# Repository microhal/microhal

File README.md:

devel: 

# microhal
Microhal is project that try to deliver Hardware Abstraction Layer (HAL) that helps you develop software faster and easier to portable to different platforms.

## microhal API
We provide API for:
- GPIO
- External Inettupts
- Serial Ports
- SPI
- I2C

## Supported platforms
STM32F4xx, STM32F3xx <br>
Currently we are testing our software on:<br>
- STM32F407VGT6
- STM32F411RE
- STM32F344R8

## Device drivers
With microhal we provide device drivers working above our HAL.
List of supported devices:
- BMP180
- DS2782
- DS2786
- HX711 (SPI Implementation)
- ISL29023
- Lepton IR Cammera
- LIS2DH12
- LIS302
- LIS3DSH
- LSM330DL
- M24C16
- MAG3110
- MPL115A2
- MPL3115A2
- MRF89XA
- PCF8563
- RFM70
- SHT21
- TMP006
- uCAM-II
- WS2812 (SPI Implementation)

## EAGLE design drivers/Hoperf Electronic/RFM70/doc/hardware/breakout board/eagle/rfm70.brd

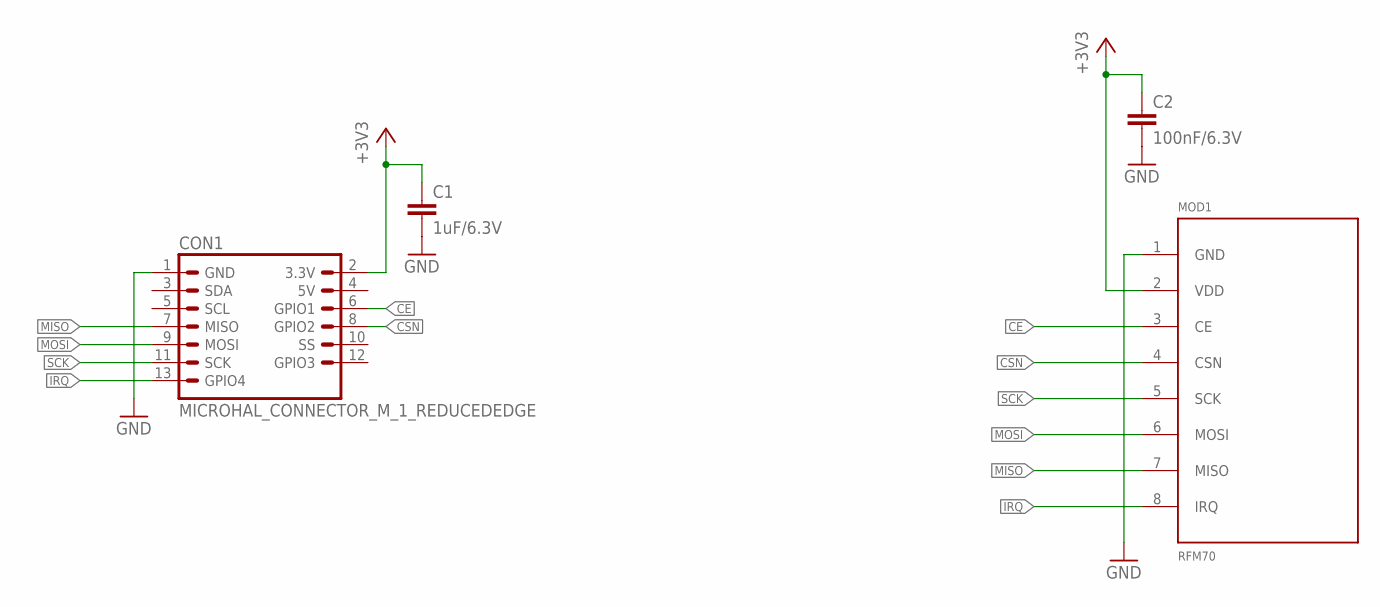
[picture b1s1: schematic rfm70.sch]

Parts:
C1: 1uF/6.3V; C0603K
C2: 100nF/6.3V; C0603K
CON1: MICROHAL_CONNECTOR_M_1_REDUCEDEDGE; MICROHAL_CONNECTOR_M_1_REDUCED_EDGE
MOD1: RFM70; RFM70_PACK

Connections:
+3V3: C1.1, C2.1, CON1.2 (3.3V), MOD1.2 (VDD)
CE: CON1.6 (GPIO1), MOD1.3 (CE)
CSN: CON1.8 (GPIO2), MOD1.4 (CSN)
GND: C1.2, C2.2, CON1.1 (GND), MOD1.1 (GND)
IRQ: CON1.13 (GPIO4), MOD1.8 (IRQ)
MISO: CON1.7 (MISO), MOD1.7 (MISO)
MOSI: CON1.9 (MOSI), MOD1.6 (MOSI)
SCK: CON1.11 (SCK), MOD1.5 (SCK)

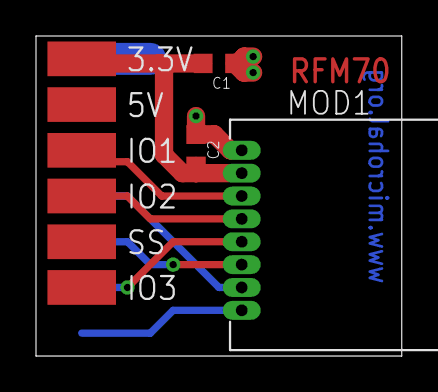
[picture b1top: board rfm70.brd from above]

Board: 2 copper layers, 20.3 x 17.8 mm, 4 parts (0 on the bottom side), 8 nets.

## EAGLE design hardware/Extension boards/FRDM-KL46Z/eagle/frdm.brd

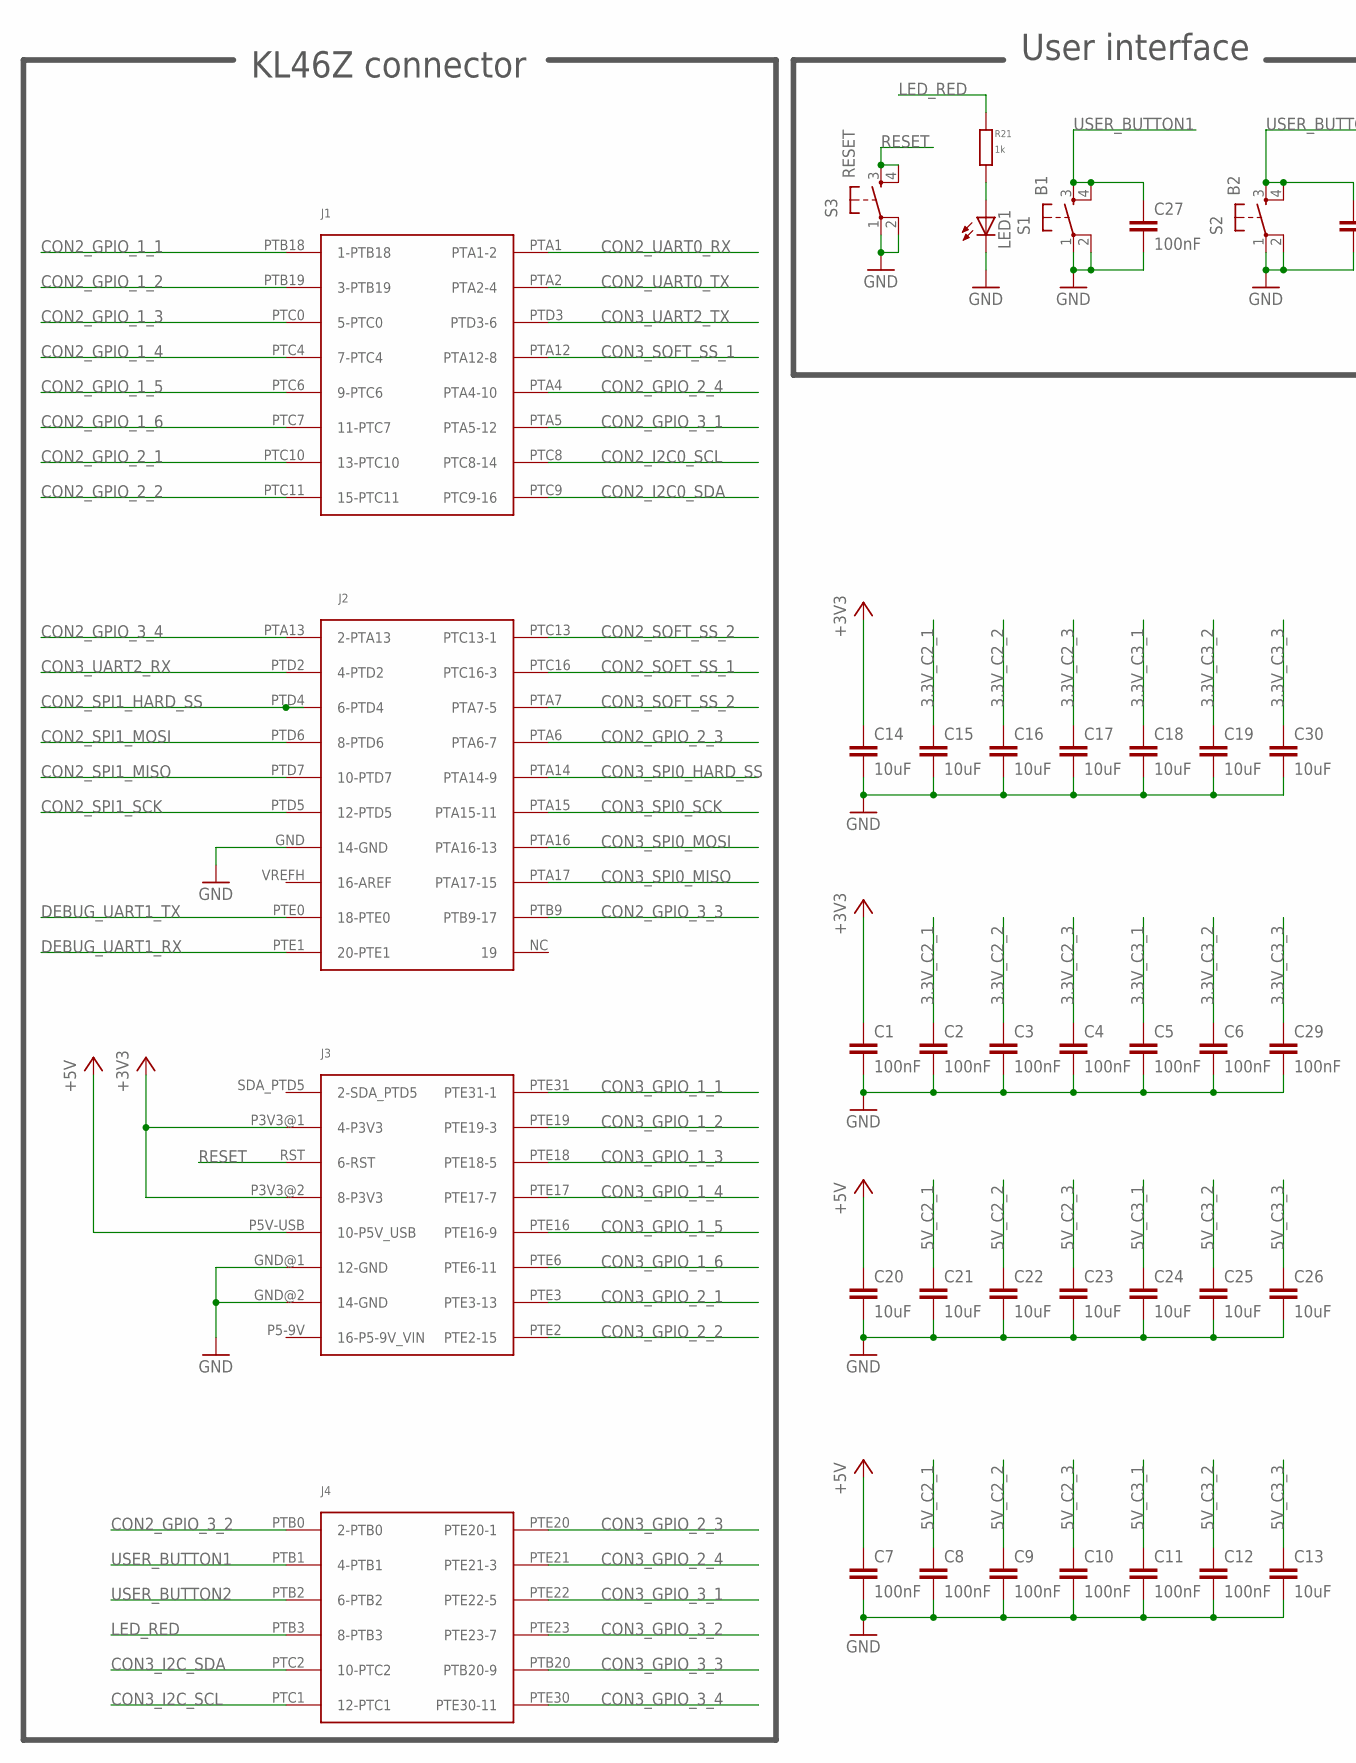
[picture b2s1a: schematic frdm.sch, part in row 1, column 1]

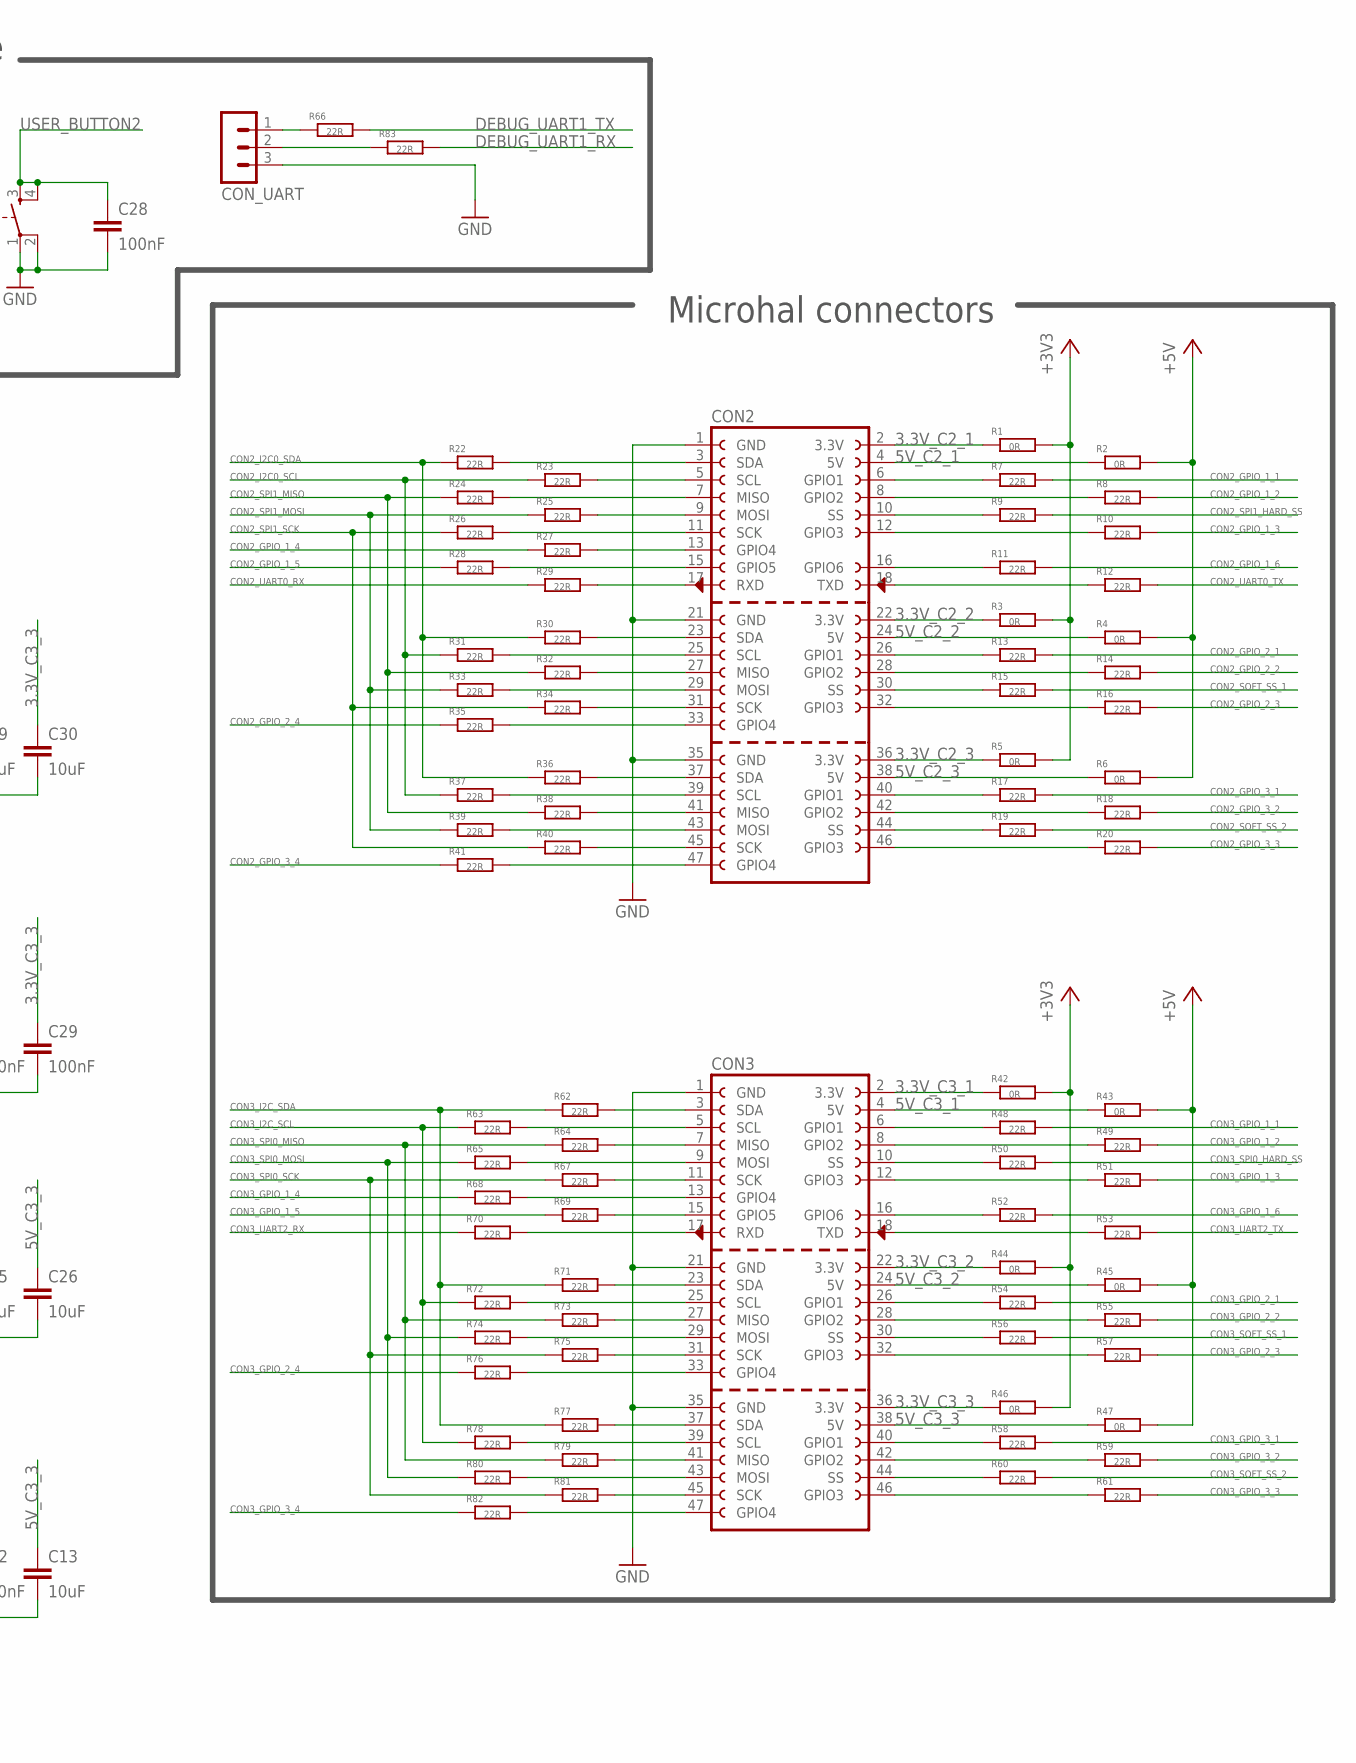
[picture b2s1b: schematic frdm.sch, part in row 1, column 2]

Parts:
C1, C2, C3, C4, C5, C6, C7, C8, C9, C10, C11, C12, C27, C28, C29: 100nF; C0603K
C13, C14, C15, C16, C17, C18, C19, C20, C21, C22, C23, C24, C25, C26, C30: 10uF; C0603K
CON1: FRDM_BASE
CON2, CON3: MICROHAL_CONNECTOR_F_3
CON_UART: MA03-1
LED1: LEDCHIPLED_0603; CHIPLED_0603
R1, R2, R3, R4, R5, R6, R42, R43, R44, R45, R46, R47: 0R; R0603
R7, R8, R9, R10, R11, R12, R13, R14, R15, R16, R17, R18, R19, R20, R22, R23, R24, R25, R26, R27, R28, R29, R30, R31, R32, R33, R34, R35, R36, R37, R38, R39, R40, R41, R48, R49, R50, R51, R52, R53, R54, R55, R56, R57, R58, R59, R60, R61, R62, R63, R64, R65, R66, R67, R68, R69, R70, R71, R72, R73, R74, R75, R76, R77, R78, R79, R80, R81, R82, R83: 22R; R0603
R21: 1k; R0603
S1: B1; SWITCH_TACT_6X6_SMD
S2: B2; SWITCH_TACT_6X6_SMD
S3: RESET; SWITCH_TACT_6X6_SMD

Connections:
3.3V_C2_1: C2.1, C15.1, CON2.2 (3.3V), R1.1
3.3V_C2_2: C3.1, C16.1, CON2.22 (3.3V), R3.1
3.3V_C2_3: C4.1, C17.1, CON2.36 (3.3V), R5.1
3.3V_C3_1: C5.1, C18.1, CON3.2 (3.3V), R42.1
3.3V_C3_2: C6.1, C19.1, CON3.22 (3.3V), R44.1
3.3V_C3_3: C29.1, C30.1, CON3.36 (3.3V), R46.1
5V_C2_1: C8.1, C21.1, CON2.4 (5V), R2.1
5V_C2_2: C9.1, C22.1, CON2.24 (5V), R4.1
5V_C2_3: C10.1, C23.1, CON2.38 (5V), R6.1
5V_C3_1: C11.1, C24.1, CON3.4 (5V), R43.1
5V_C3_2: C12.1, C25.1, CON3.24 (5V), R45.1
5V_C3_3: C13.1, C26.1, CON3.38 (5V), R47.1
+3V3: C1.1, C14.1, CON1.P3V3@1 (4-P3V3), CON1.P3V3@2 (8-P3V3), R1.2, R3.2, R5.2, R42.2, R44.2, R46.2
+5V: C7.1, C20.1, CON1.P5V-USB (10-P5V_USB), R2.2, R4.2, R6.2, R43.2, R45.2, R47.2
CON2_GPIO_1_1: CON1.PTB18 (1-PTB18), R7.2
CON2_GPIO_1_2: CON1.PTB19 (3-PTB19), R8.2
CON2_GPIO_1_3: CON1.PTC0 (5-PTC0), R10.2
CON2_GPIO_1_4: CON1.PTC4 (7-PTC4), R27.1
CON2_GPIO_1_5: CON1.PTC6 (9-PTC6), R28.1
CON2_GPIO_1_6: CON1.PTC7 (11-PTC7), R11.2
CON2_GPIO_2_1: CON1.PTC10 (13-PTC10), R13.2
CON2_GPIO_2_2: CON1.PTC11 (15-PTC11), R14.2
CON2_GPIO_2_3: CON1.PTA6 (PTA6-7), R16.2
CON2_GPIO_2_4: CON1.PTA4 (PTA4-10), R35.1
CON2_GPIO_3_1: CON1.PTA5 (PTA5-12), R17.2
CON2_GPIO_3_2: CON1.PTB0 (2-PTB0), R18.2
CON2_GPIO_3_3: CON1.PTB9 (PTB9-17), R20.2
CON2_GPIO_3_4: CON1.PTA13 (2-PTA13), R41.1
CON2_I2C0_SCL: CON1.PTC8 (PTC8-14), R23.1, R31.1, R37.1
CON2_I2C0_SDA: CON1.PTC9 (PTC9-16), R22.1, R30.1, R36.1
CON2_SOFT_SS_1: CON1.PTC16 (PTC16-3), R15.2
CON2_SOFT_SS_2: CON1.PTC13 (PTC13-1), R19.2
CON2_SPI1_HARD_SS: CON1.PTD4 (6-PTD4), R9.2
CON2_SPI1_MISO: CON1.PTD7 (10-PTD7), R24.1, R32.1, R38.1
CON2_SPI1_MOSI: CON1.PTD6 (8-PTD6), R25.1, R33.1, R39.1
CON2_SPI1_SCK: CON1.PTD5 (12-PTD5), R26.1, R34.1, R40.1
CON2_UART0_RX: CON1.PTA1 (PTA1-2), R29.1
CON2_UART0_TX: CON1.PTA2 (PTA2-4), R12.2
CON3_GPIO_1_1: CON1.PTE31 (PTE31-1), R48.2
CON3_GPIO_1_2: CON1.PTE19 (PTE19-3), R49.2
CON3_GPIO_1_3: CON1.PTE18 (PTE18-5), R51.2
CON3_GPIO_1_4: CON1.PTE17 (PTE17-7), R68.1
CON3_GPIO_1_5: CON1.PTE16 (PTE16-9), R69.1
CON3_GPIO_1_6: CON1.PTE6 (PTE6-11), R52.2
CON3_GPIO_2_1: CON1.PTE3 (PTE3-13), R54.2
CON3_GPIO_2_2: CON1.PTE2 (PTE2-15), R55.2
CON3_GPIO_2_3: CON1.PTE20 (PTE20-1), R57.2
CON3_GPIO_2_4: CON1.PTE21 (PTE21-3), R76.1
CON3_GPIO_3_1: CON1.PTE22 (PTE22-5), R58.2
CON3_GPIO_3_2: CON1.PTE23 (PTE23-7), R59.2
CON3_GPIO_3_3: CON1.PTB20 (PTB20-9), R61.2
CON3_GPIO_3_4: CON1.PTE30 (PTE30-11), R82.1
CON3_I2C_SCL: CON1.PTC1 (12-PTC1), R63.1, R72.1, R78.1
CON3_I2C_SDA: CON1.PTC2 (10-PTC2), R62.1, R71.1, R77.1
CON3_SOFT_SS_1: CON1.PTA12 (PTA12-8), R56.2
CON3_SOFT_SS_2: CON1.PTA7 (PTA7-5), R60.2
CON3_SPI0_HARD_SS: CON1.PTA14 (PTA14-9), R50.2
CON3_SPI0_MISO: CON1.PTA17 (PTA17-15), R64.1, R73.1, R79.1
CON3_SPI0_MOSI: CON1.PTA16 (PTA16-13), R65.1, R74.1, R80.1
CON3_SPI0_SCK: CON1.PTA15 (PTA15-11), R67.1, R75.1, R81.1
CON3_UART2_RX: CON1.PTD2 (4-PTD2), R70.1
CON3_UART2_TX: CON1.PTD3 (PTD3-6), R53.2
DEBUG_UART1_RX: CON1.PTE1 (20-PTE1), R83.2
DEBUG_UART1_TX: CON1.PTE0 (18-PTE0), R66.2
GND: C1.2, C2.2, C3.2, C4.2, C5.2, C6.2, C7.2, C8.2, C9.2, C10.2, C11.2, C12.2, C13.2, C14.2, C15.2, C16.2, C17.2, C18.2, C19.2, C20.2, C21.2, C22.2, C23.2, C24.2, C25.2, C26.2, C27.2, C28.2, C29.2, C30.2, CON1.GND (14-GND), CON1.GND@1 (12-GND), CON1.GND@2 (14-GND), CON2.1 (GND), CON2.21 (GND), CON2.35 (GND), CON3.1 (GND), CON3.21 (GND), CON3.35 (GND), CON_UART.3, LED1.C, S1.1, S1.2, S2.1, S2.2, S3.1, S3.2
LED_RED: CON1.PTB3 (8-PTB3), R21.2
unnamed: CON2.7 (MISO), R24.2
unnamed: CON2.6 (GPIO1), R7.1
unnamed: CON2.8 (GPIO2), R8.1
unnamed: CON3.9 (MOSI), R65.2
unnamed: CON3.5 (SCL), R63.2
unnamed: CON3.13 (GPIO4), R68.2
unnamed: CON3.11 (SCK), R67.2
unnamed: CON3.15 (GPIO5), R69.2
unnamed: CON2.10 (SS), R9.1
unnamed: CON2.12 (GPIO3), R10.1
unnamed: CON2.16 (GPIO6), R11.1
unnamed: CON3.7 (MISO), R64.2
unnamed: CON2.18 (TXD), R12.1
unnamed: CON2.26 (GPIO1), R13.1
unnamed: CON3.6 (GPIO1), R48.1
unnamed: CON2.28 (GPIO2), R14.1
unnamed: CON2.30 (SS), R15.1
unnamed: CON2.32 (GPIO3), R16.1
unnamed: CON_UART.1, R66.1
unnamed: CON_UART.2, R83.1
unnamed: CON3.8 (GPIO2), R49.1
unnamed: CON2.40 (GPIO1), R17.1
unnamed: CON2.44 (SS), R19.1
unnamed: CON2.42 (GPIO2), R18.1
unnamed: CON2.46 (GPIO3), R20.1
unnamed: CON3.10 (SS), R50.1
unnamed: CON3.12 (GPIO3), R51.1
unnamed: CON3.16 (GPIO6), R52.1
unnamed: CON3.18 (TXD), R53.1
unnamed: CON3.26 (GPIO1), R54.1
unnamed: CON3.30 (SS), R56.1
unnamed: CON3.28 (GPIO2), R55.1
unnamed: CON3.32 (GPIO3), R57.1
unnamed: CON2.47 (GPIO4), R41.2
unnamed: CON2.45 (SCK), R40.2
unnamed: CON2.43 (MOSI), R39.2
unnamed: CON2.41 (MISO), R38.2
unnamed: CON2.39 (SCL), R37.2
unnamed: CON2.37 (SDA), R36.2
unnamed: CON2.33 (GPIO4), R35.2
unnamed: CON2.31 (SCK), R34.2
unnamed: CON2.29 (MOSI), R33.2
unnamed: CON2.27 (MISO), R32.2
unnamed: CON2.25 (SCL), R31.2
unnamed: CON2.23 (SDA), R30.2
unnamed: CON2.17 (RXD), R29.2
unnamed: CON2.13 (GPIO4), R27.2
unnamed: CON2.9 (MOSI), R25.2
unnamed: CON2.5 (SCL), R23.2
unnamed: CON2.3 (SDA), R22.2
unnamed: CON2.11 (SCK), R26.2
unnamed: CON2.15 (GPIO5), R28.2
unnamed: CON3.40 (GPIO1), R58.1
unnamed: CON3.42 (GPIO2), R59.1
unnamed: CON3.44 (SS), R60.1
unnamed: CON3.46 (GPIO3), R61.1
unnamed: CON3.47 (GPIO4), R82.2
unnamed: CON3.45 (SCK), R81.2
unnamed: CON3.43 (MOSI), R80.2
unnamed: CON3.41 (MISO), R79.2
unnamed: CON3.39 (SCL), R78.2
unnamed: CON3.37 (SDA), R77.2
unnamed: CON3.33 (GPIO4), R76.2
unnamed: CON3.31 (SCK), R75.2
unnamed: CON3.29 (MOSI), R74.2
unnamed: CON3.27 (MISO), R73.2
unnamed: CON3.25 (SCL), R72.2
unnamed: CON3.23 (SDA), R71.2
unnamed: CON3.17 (RXD), R70.2
unnamed: CON3.3 (SDA), R62.2
unnamed: LED1.A, R21.1
RESET: CON1.RST (6-RST), S3.3, S3.4
USER_BUTTON1: C27.1, CON1.PTB1 (4-PTB1), S1.3, S1.4
USER_BUTTON2: C28.1, CON1.PTB2 (6-PTB2), S2.3, S2.4

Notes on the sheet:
KL46Z connector
User interface
Microhal connectors

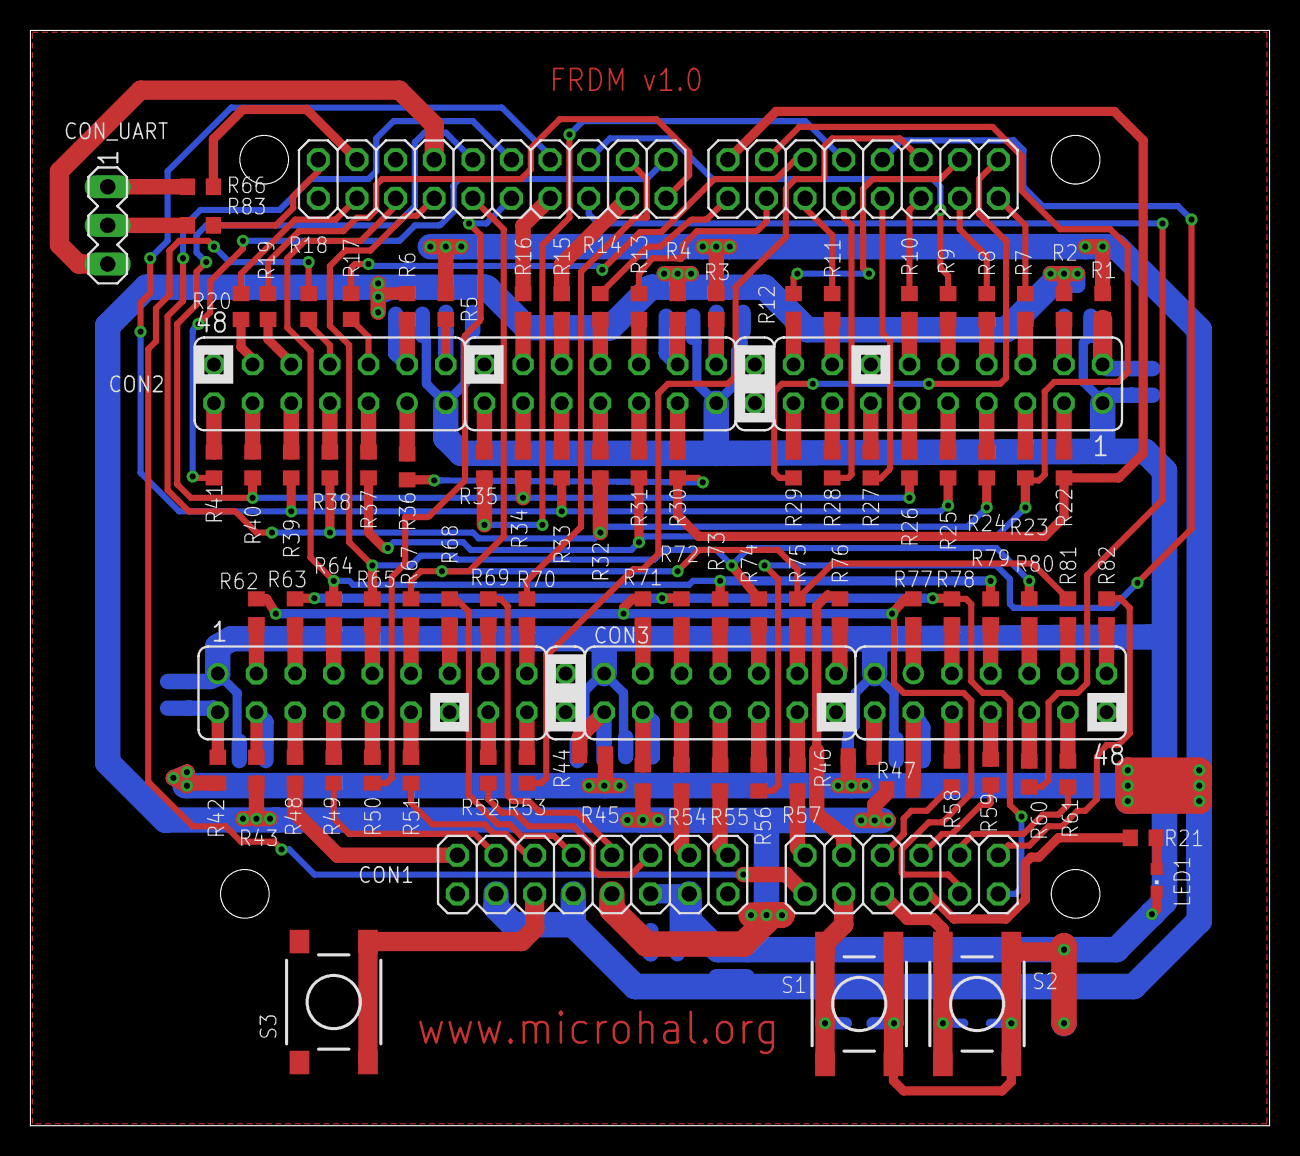
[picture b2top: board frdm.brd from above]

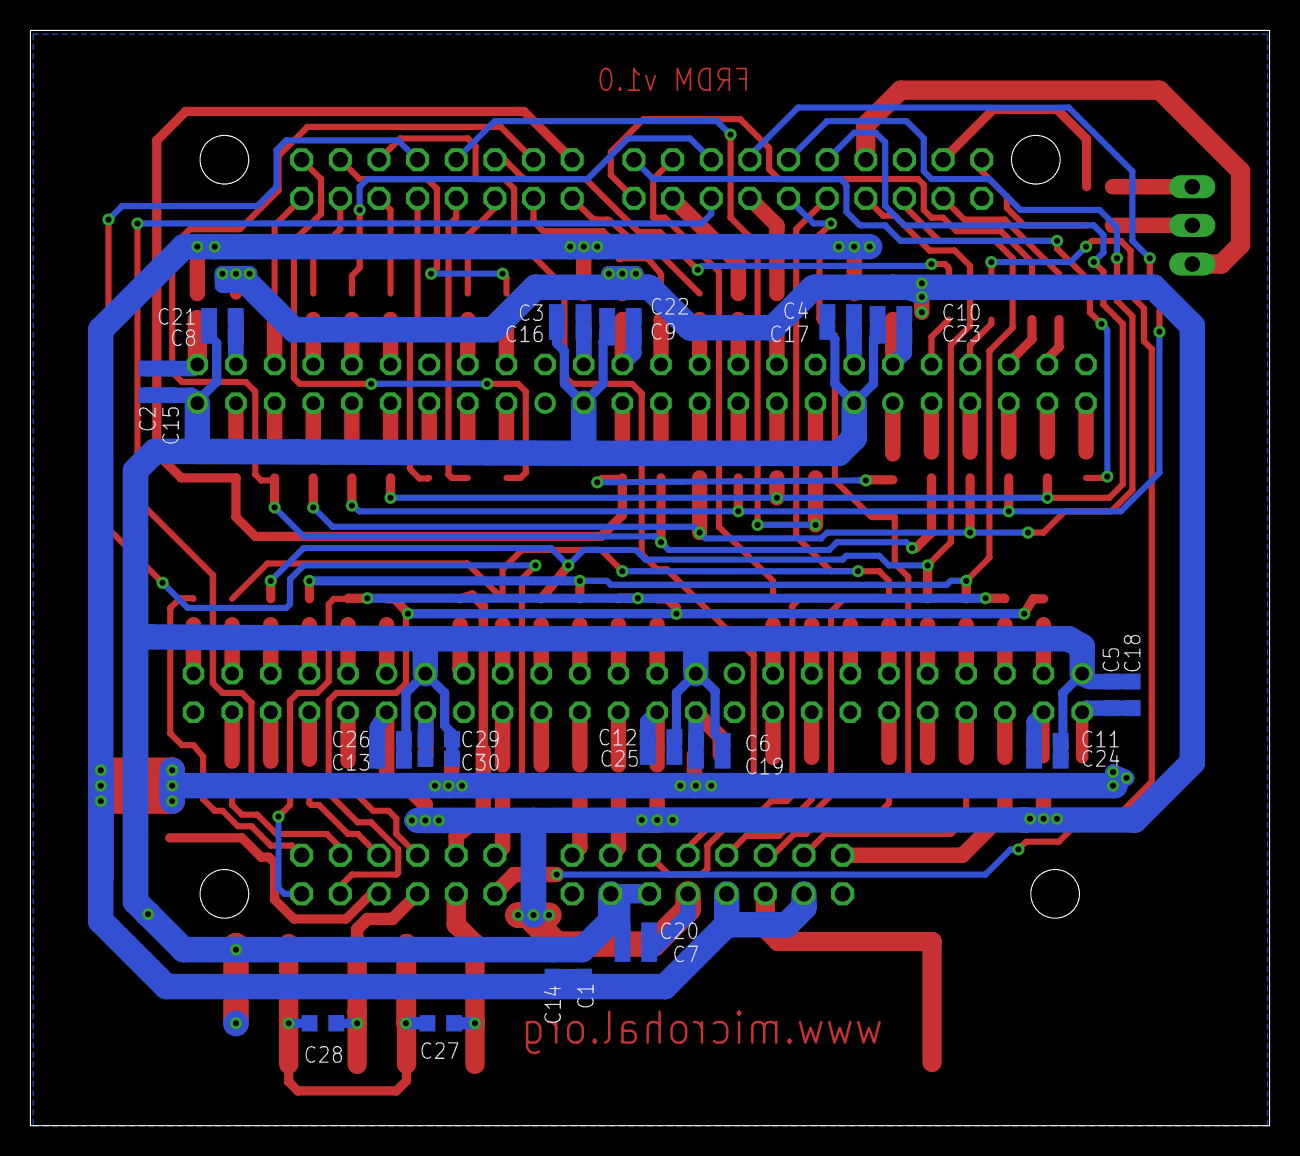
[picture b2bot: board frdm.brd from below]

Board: 2 copper layers, 81.5 x 72.0 mm, 121 parts (30 on the bottom side), 140 nets.

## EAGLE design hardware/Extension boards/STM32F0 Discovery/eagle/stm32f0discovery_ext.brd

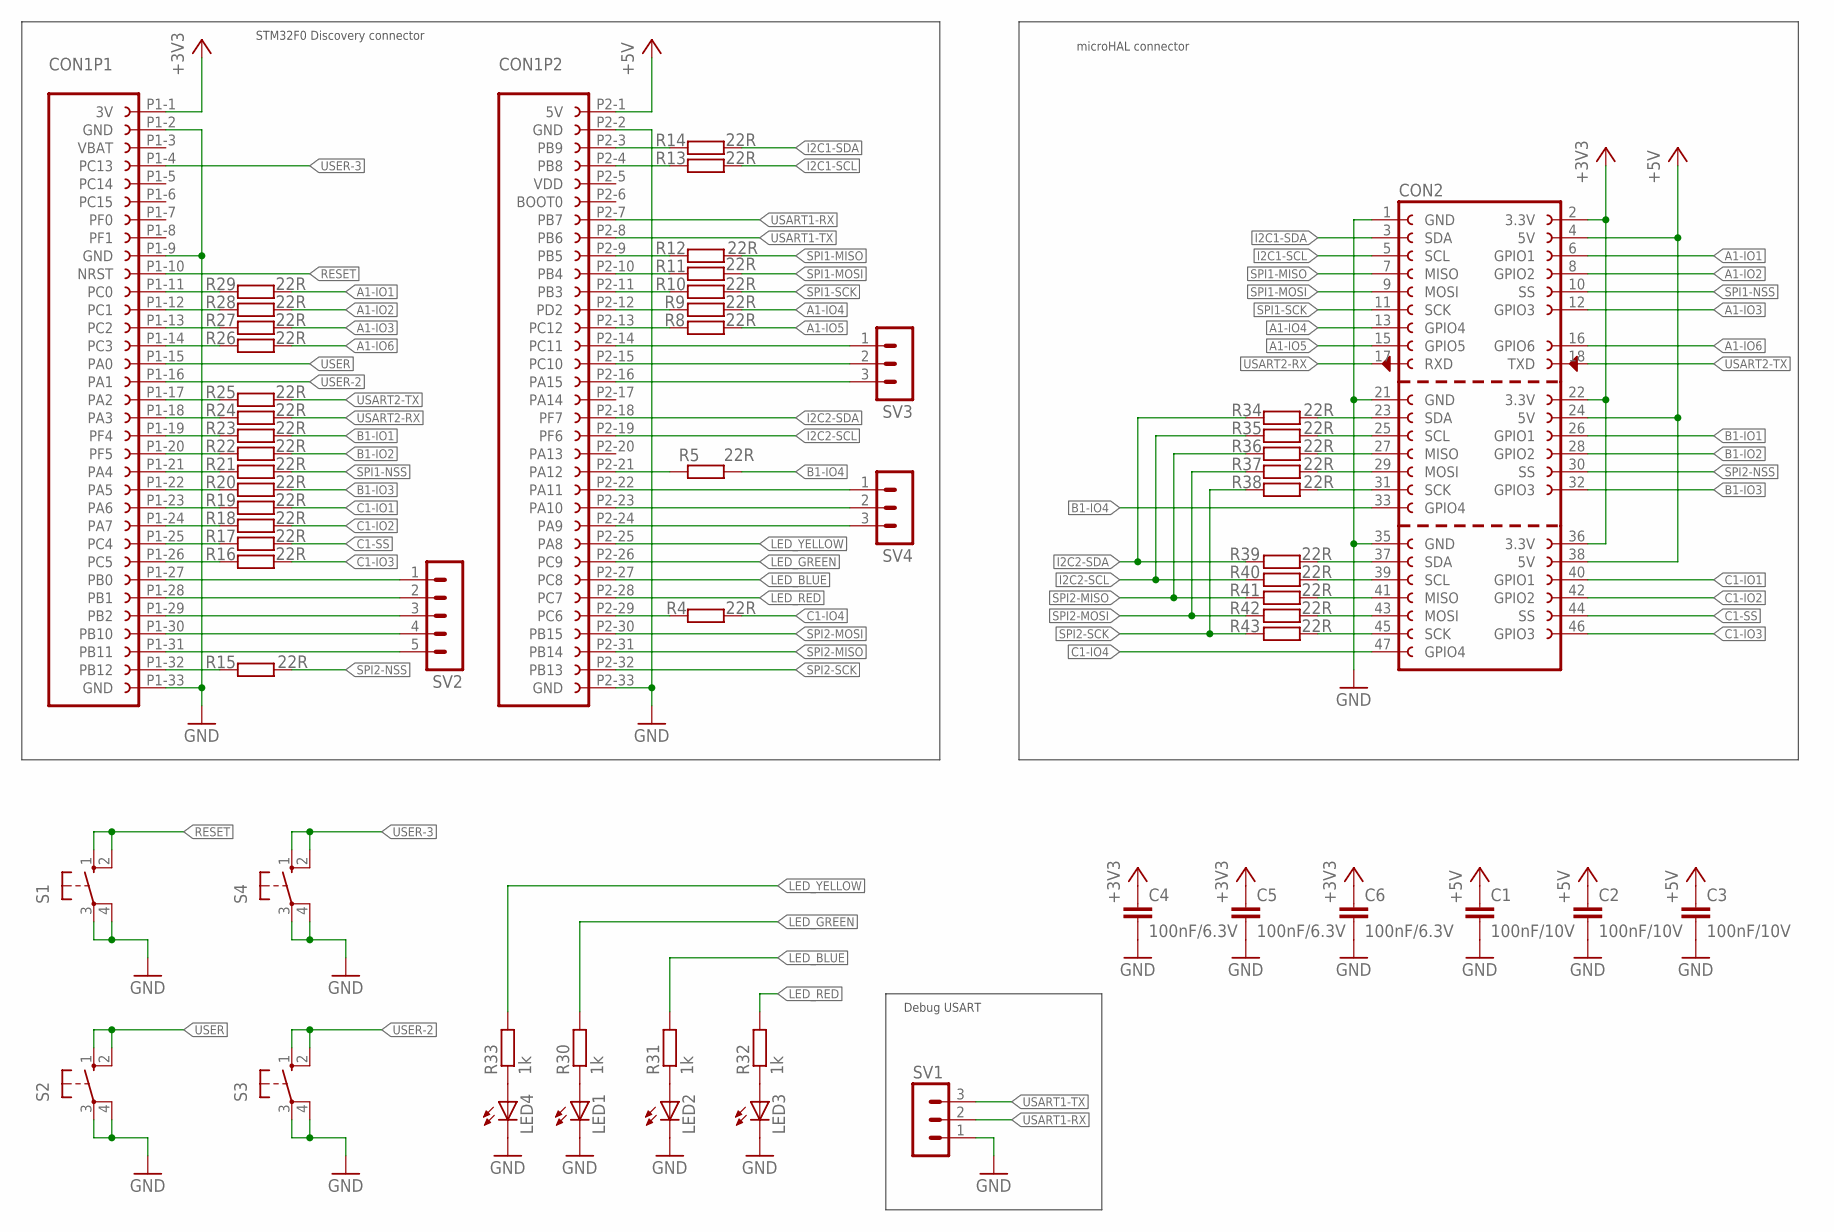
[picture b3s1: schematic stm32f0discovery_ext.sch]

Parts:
C1, C2, C3: 100nF/10V; C0603K
C4, C5, C6: 100nF/6.3V; C0603K
CON1: STM32F0-DISCOVERY; STM32F0-DISCOVERY-CONNECTOR
CON2: MICROHAL_CONNECTOR_F_3
LED1, LED2, LED3, LED4: LEDCHIPLED_0603; CHIPLED_0603
R4, R5, R8, R9, R10, R11, R12, R13, R14, R15, R16, R17, R18, R19, R20, R21, R22, R23, R24, R25, R26, R27, R28, R29, R34, R35, R36, R37, R38, R39, R40, R41, R42, R43: 22R; R0603
R30, R31, R32, R33: 1k; R0603
S1, S2, S3, S4: 10-XX; B3F-10XX
SV1, SV3, SV4: MA03-1
SV2: MA05-1

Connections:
+3V3: C4.1, C5.1, C6.1, CON1.P1-1 (3V), CON2.2 (3.3V), CON2.22 (3.3V), CON2.36 (3.3V)
+5V: C1.1, C2.1, C3.1, CON1.P2-1 (5V), CON2.4 (5V), CON2.24 (5V), CON2.38 (5V)
A1-IO1: CON2.6 (GPIO1), R29.2
A1-IO2: CON2.8 (GPIO2), R28.2
A1-IO3: CON2.12 (GPIO3), R27.2
A1-IO4: CON2.13 (GPIO4), R9.2
A1-IO5: CON2.15 (GPIO5), R8.2
A1-IO6: CON2.16 (GPIO6), R26.2
B1-IO1: CON2.26 (GPIO1), R23.2
B1-IO2: CON2.28 (GPIO2), R22.2
B1-IO3: CON2.32 (GPIO3), R20.2
B1-IO4: CON2.33 (GPIO4), R5.2
C1-IO1: CON2.40 (GPIO1), R19.2
C1-IO2: CON2.42 (GPIO2), R18.2
C1-IO3: CON2.46 (GPIO3), R16.2
C1-IO4: CON2.47 (GPIO4), R4.2
C1-SS: CON2.44 (SS), R17.2
GND: C1.2, C2.2, C3.2, C4.2, C5.2, C6.2, CON1.P1-2 (GND), CON1.P1-9 (GND), CON1.P1-33 (GND), CON1.P2-2 (GND), CON1.P2-33 (GND), CON2.1 (GND), CON2.21 (GND), CON2.35 (GND), LED1.C, LED2.C, LED3.C, LED4.C, S1.3, S1.4 (P1), S2.3, S2.4 (P1), S3.3, S3.4 (P1), S4.3, S4.4 (P1), SV1.1
I2C1-SCL: CON2.5 (SCL), R13.2
I2C1-SDA: CON2.3 (SDA), R14.2
I2C2-SCL: CON1.P2-19 (PF6), R35.1, R40.1
I2C2-SDA: CON1.P2-18 (PF7), R34.1, R39.1
LED_BLUE: CON1.P2-27 (PC8), R31.2
LED_GREEN: CON1.P2-26 (PC9), R30.2
LED_RED: CON1.P2-28 (PC7), R32.2
LED_YELLOW: CON1.P2-25 (PA8), R33.2
unnamed: CON1.P2-29 (PC6), R4.1
unnamed: CON1.P2-21 (PA12), R5.1
unnamed: CON1.P2-13 (PC12), R8.1
unnamed: CON1.P2-12 (PD2), R9.1
unnamed: CON1.P2-11 (PB3), R10.1
unnamed: CON1.P2-10 (PB4), R11.1
unnamed: CON1.P2-9 (PB5), R12.1
unnamed: CON1.P2-4 (PB8), R13.1
unnamed: CON1.P2-3 (PB9), R14.1
unnamed: CON1.P1-32 (PB12), R15.1
unnamed: CON1.P1-26 (PC5), R16.1
unnamed: CON1.P1-25 (PC4), R17.1
unnamed: CON1.P1-24 (PA7), R18.1
unnamed: CON1.P1-23 (PA6), R19.1
unnamed: CON1.P1-22 (PA5), R20.1
unnamed: CON1.P1-21 (PA4), R21.1
unnamed: CON1.P1-20 (PF5), R22.1
unnamed: CON1.P1-19 (PF4), R23.1
unnamed: CON1.P1-18 (PA3), R24.1
unnamed: CON1.P1-17 (PA2), R25.1
unnamed: CON1.P1-14 (PC3), R26.1
unnamed: CON1.P1-13 (PC2), R27.1
unnamed: CON1.P1-12 (PC1), R28.1
unnamed: CON1.P1-11 (PC0), R29.1
unnamed: LED1.A, R30.1
unnamed: LED2.A, R31.1
unnamed: LED3.A, R32.1
unnamed: LED4.A, R33.1
unnamed: CON1.P1-27 (PB0), SV2.1
unnamed: CON1.P1-28 (PB1), SV2.2
unnamed: CON1.P1-29 (PB2), SV2.3
unnamed: CON1.P1-30 (PB10), SV2.4
unnamed: CON1.P1-31 (PB11), SV2.5
unnamed: CON1.P2-14 (PC11), SV3.1
unnamed: CON1.P2-15 (PC10), SV3.2
unnamed: CON1.P2-16 (PA15), SV3.3
unnamed: CON1.P2-22 (PA11), SV4.1
unnamed: CON1.P2-23 (PA10), SV4.2
unnamed: CON1.P2-24 (PA9), SV4.3
unnamed: CON2.23 (SDA), R34.2
unnamed: CON2.25 (SCL), R35.2
unnamed: CON2.27 (MISO), R36.2
unnamed: CON2.29 (MOSI), R37.2
unnamed: CON2.31 (SCK), R38.2
unnamed: CON2.37 (SDA), R39.2
unnamed: CON2.39 (SCL), R40.2
unnamed: CON2.41 (MISO), R41.2
unnamed: CON2.43 (MOSI), R42.2
unnamed: CON2.45 (SCK), R43.2
RESET: CON1.P1-10 (NRST), S1.1 (S), S1.2 (S1)
SPI1-MISO: CON2.7 (MISO), R12.2
SPI1-MOSI: CON2.9 (MOSI), R11.2
SPI1-NSS: CON2.10 (SS), R21.2
SPI1-SCK: CON2.11 (SCK), R10.2
SPI2-MISO: CON1.P2-31 (PB14), R36.1, R41.1
SPI2-MOSI: CON1.P2-30 (PB15), R37.1, R42.1
SPI2-NSS: CON2.30 (SS), R15.2
SPI2-SCK: CON1.P2-32 (PB13), R38.1, R43.1
USART1-RX: CON1.P2-7 (PB7), SV1.2
USART1-TX: CON1.P2-8 (PB6), SV1.3
USART2-RX: CON2.17 (RXD), R24.2
USART2-TX: CON2.18 (TXD), R25.2
USER: CON1.P1-15 (PA0), S2.1 (S), S2.2 (S1)
USER-2: CON1.P1-16 (PA1), S3.1 (S), S3.2 (S1)
USER-3: CON1.P1-4 (PC13), S4.1 (S), S4.2 (S1)

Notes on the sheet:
STM32F0 Discovery connector
microHAL connector
Debug USART

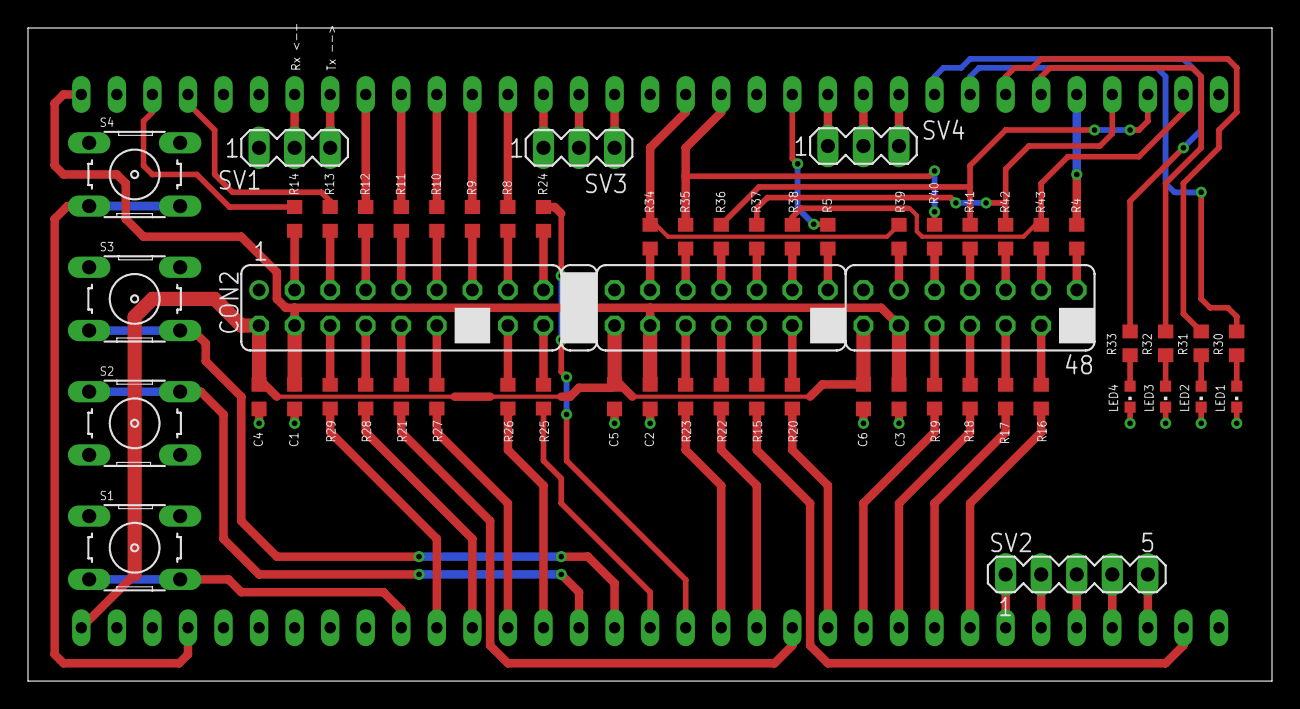
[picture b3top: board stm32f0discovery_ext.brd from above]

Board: 2 copper layers, 88.9 x 46.7 mm, 58 parts (1 on the bottom side), 91 nets.

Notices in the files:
microhal/ports/lpc43xx/gpio_lpc43xx.h:
@copyright  Pawel Okas
@copyright Copyright (c) 2019, Pawel Okas
All rights reserved.
parts and their libraries:
mpl115a2: Copyright (c) 2016, microHAL
